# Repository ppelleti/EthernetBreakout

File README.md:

This repository contains KiCad 4.x files for a small breakout board
which allows an Ethernet jack (with built-in magnetics) to be used on
a breadboard.  For example usage, see
[this blog post](https://funwithsoftware.org/posts/2019-09-04-breadboard-ethernet-part1.html).

* [View schematic](RJ45.pdf)
* [View PCB](https://eyrie.io/board/d35531e8b100497399c27f16be3ca795)
* [Order board from OSH Park](https://oshpark.com/shared_projects/zE8d2y9D)

## Bill of Materials

* [Amphenol RJMG1BD3B8K1ANR MagJack](https://www.digikey.com/product-detail/en/amphenol-commercial-products/RJMG1BD3B8K1ANR/RJMG1BD3B8K1ANR-ND/5359794)
* 2 strips of male header, 6 pins each

## Pins

* **TD+, TCT, and TD-**: positive, center tap, and negative pin for the transmit side
* **TD+, RCT, and RD-**: ditto for receive side
* **GND**: ground pin on the MagJack
* **SHLD**: metal housing of the MagJack
* **G_A and G_K**: anode and cathode for the green LED
* **Y_A and Y_K**: ditto for the yellow LED

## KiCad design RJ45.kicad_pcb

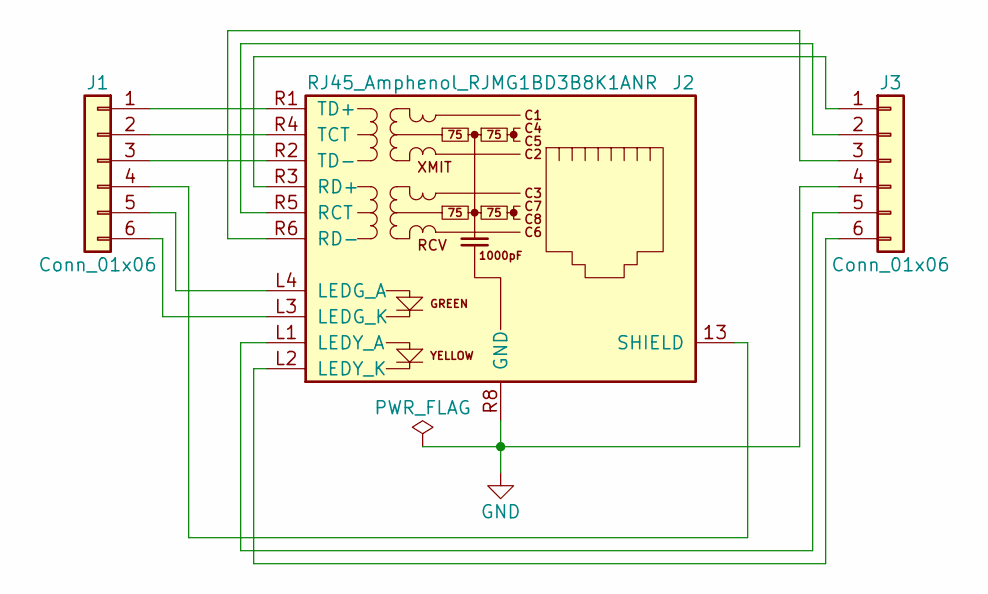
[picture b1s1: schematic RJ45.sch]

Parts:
J1, J3: Conn_01x06; Pin_Header_Straight_1x06_Pitch2.54mm
J2: RJ45_Amphenol_RJMG1BD3B8K1ANR

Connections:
GND: J2.R8 (GND), J3.4
unnamed: J1.1, J2.R1 (TD+)
unnamed: J1.2, J2.R4 (TCT)
unnamed: J1.3, J2.R2 (TD-)
unnamed: J1.4, J2.13 (SHIELD)
unnamed: J1.5, J2.L4 (LEDG_A)
unnamed: J1.6, J2.L3 (LEDG_K)
unnamed: J2.L1 (LEDY_A), J3.5
unnamed: J2.L2 (LEDY_K), J3.6
unnamed: J2.R3 (RD+), J3.1
unnamed: J2.R5 (RCT), J3.2
unnamed: J2.R6 (RD-), J3.3

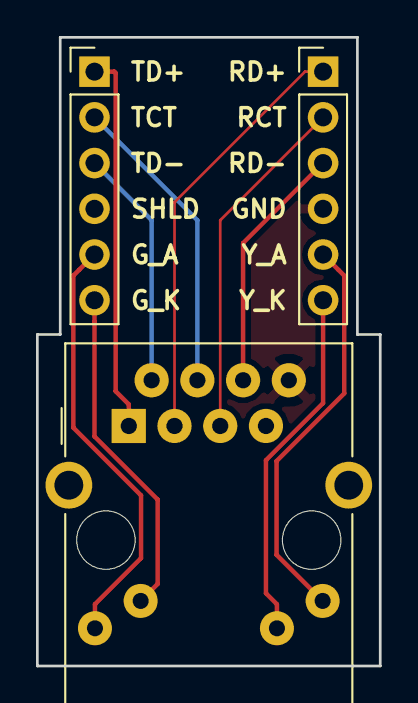
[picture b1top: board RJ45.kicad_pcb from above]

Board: 2 copper layers, 19.1 x 34.9 mm, 3 parts (0 on the bottom side), 12 nets.

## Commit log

2018-04-25 Initial commit.
2018-04-25 Let KiCad reorder things.
2018-04-25 Add myLibrary to project.
2018-04-25 Draw schematic.
2018-04-25 Add myLibrary.pretty to fp-lib-table.
2018-04-25 Associate footprints.
2018-04-25 Draw tracks.
2018-04-25 Rearrange to make narrower.
2018-04-25 Draw board outline.
2018-04-25 Label pins on silkscreen.
2018-04-25 Route tracks.
2018-04-25 Add filled zones.
2018-04-25 Fill zones.
2018-04-25 Text on back silkscreen.
2018-04-25 Add metadata.
2019-03-02 Add README, photo, and schematic.
2019-09-05 Update README, picture, and license.
2019-09-05 Link to OSH Park and eyrie.io.
2019-09-05 Two six-pin headers.
